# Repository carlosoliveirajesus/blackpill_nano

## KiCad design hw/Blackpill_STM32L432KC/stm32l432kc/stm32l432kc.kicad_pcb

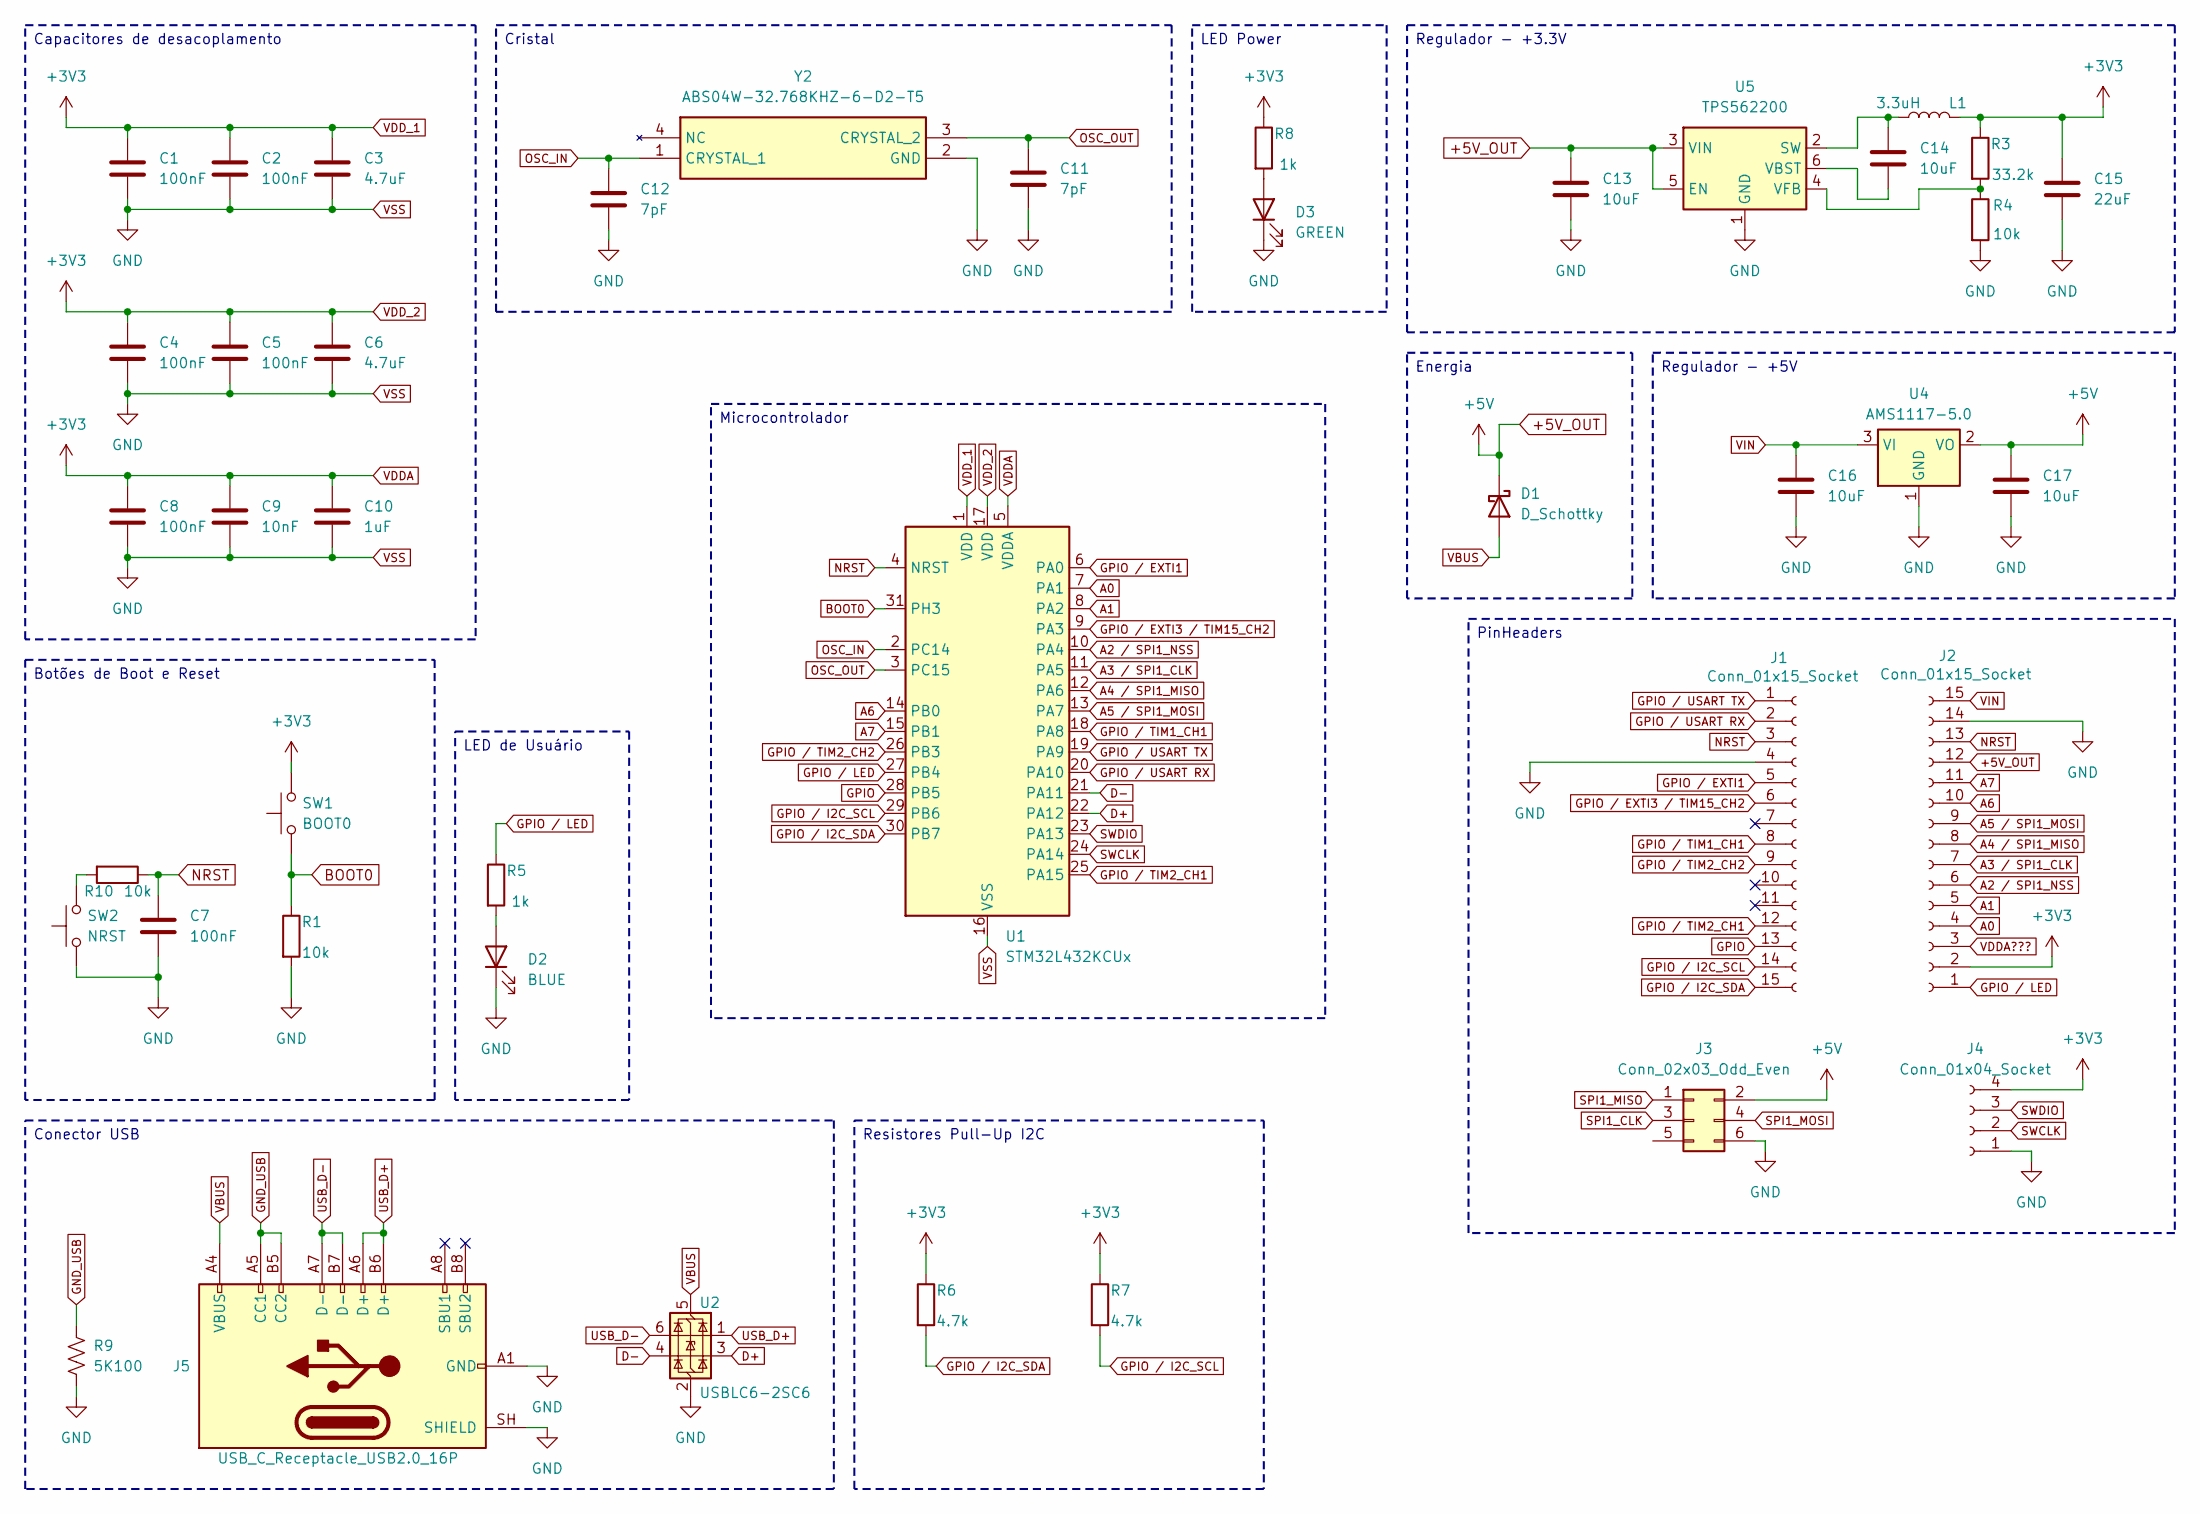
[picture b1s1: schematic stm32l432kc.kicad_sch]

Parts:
C1, C2, C4, C5, C7, C8: 100nF; C_0402_1005Metric
C3, C6: 4.7uF; C_0402_1005Metric
C9: 10nF; C_0402_1005Metric
C10: 1uF; C_0402_1005Metric
C11, C12: 7pF; C_0201_0603Metric
C13, C14, C16, C17: 10uF; C_0402_1005Metric
C15: 22uF; C_0201_0603Metric
D1: D_Schottky; D_SOD-123
D2: BLUE; LED_0603_1608Metric
D3: GREEN; LED_0603_1608Metric
J1, J2: Conn_01x15_Socket; PinHeader_1x15_P2.54mm_Vertical
J3: Conn_02x03_Odd_Even; PinHeader_2x03_P2.54mm_Vertical
J4: Conn_01x04_Socket; PinHeader_1x04_P2.54mm_Horizontal
J5: USB_C_Receptacle_USB2.0_16P; USB_C_Receptacle_GCT_USB4105-xx-A_16P_TopMnt_Horizontal
L1: 3.3uH; L_0603_1608Metric
R1, R4, R10: 10k; R_0402_1005Metric
R3: 33.2k; R_0402_1005Metric
R5, R8: 1k; R_0402_1005Metric
R6, R7: 4.7k; R_01005_0402Metric
R9: 5K100; R_0603_1608Metric_Pad0.98x0.95mm_HandSolder
SW1: BOOT0; SW_SPST_B3U-1000P
SW2: NRST; SW_SPST_B3U-1000P
U1: STM32L432KCUx; QFN-32-1EP_5x5mm_P0.5mm_EP3.45x3.45mm
U2: USBLC6-2SC6; SOT-23-6
U4: AMS1117-5.0; SOT-223-3_TabPin2
U5: TPS562200; SOT-23-6
Y2: ABS04W-32.768KHZ-6-D2-T5; ABS04W32768KHZ6D2T5; Mouser Part Number 815-04W-32.768-6-D2T

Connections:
+5V_OUT: C13.1, C17.1, D1.1 (K), J2.12, J3.2, U4.2 (VO), U5.3 (VIN), U5.5 (EN)
A0: J2.4, U1.7 (PA1)
A1: J2.5, U1.8 (PA2)
A2 / SPI1_NSS: J2.6, U1.10 (PA4)
A3 / SPI1_CLK: J2.7, U1.11 (PA5)
A4 / SPI1_MISO: J2.8, U1.12 (PA6)
A5 / SPI1_MOSI: J2.9, U1.13 (PA7)
A6: J2.10, U1.14 (PB0)
A7: J2.11, U1.15 (PB1)
BOOT0: R1.1, SW1.1, U1.31 (PH3)
D+: U1.22 (PA12), U2.3 (I/O2)
D-: U1.21 (PA11), U2.4 (I/O2)
GND_USB: J5.A5 (CC1), J5.B5 (CC2), R9.1
GPIO: J1.13, U1.28 (PB5)
GPIO / EXTI1: J1.5, U1.6 (PA0)
GPIO / EXTI3 / TIM15_CH2: J1.6, U1.9 (PA3)
GPIO / I2C_SCL: J1.14, R7.2, U1.29 (PB6)
GPIO / I2C_SDA: J1.15, R6.2, U1.30 (PB7)
GPIO / LED: J2.1, R5.1, U1.27 (PB4)
GPIO / TIM1_CH1: J1.8, U1.18 (PA8)
GPIO / TIM2_CH1: J1.12, U1.25 (PA15)
GPIO / TIM2_CH2: J1.9, U1.26 (PB3)
GPIO / USART RX: J1.2, U1.20 (PA10)
GPIO / USART TX: J1.1, U1.19 (PA9)
NRST: C7.1, J1.3, J2.13, R10.1, U1.4 (NRST); also elsewhere on the board
unnamed: D2.2 (A), R5.2
unnamed: D3.2 (A), R8.2
unnamed: R10.2, SW2.2
unnamed: C14.1, L1.2, U5.2 (SW)
unnamed: C14.2, U5.6 (VBST)
unnamed: R3.2, R4.1, U5.4 (VFB)
OSC_IN: C12.1, U1.2 (PC14), Y2.1 (CRYSTAL_1)
OSC_OUT: C11.1, U1.3 (PC15), Y2.3 (CRYSTAL_2)
SPI1_CLK: J3.3
SPI1_MISO: J3.1
SPI1_MOSI: J3.4
SWCLK: J4.2, U1.24 (PA14)
SWDIO: J4.3, U1.23 (PA13)
USB_D+: J5.A6 (D+), J5.B6 (D+), U2.1 (I/O1)
USB_D-: J5.A7 (D-), J5.B7 (D-), U2.6 (I/O1)
VBUS: D1.2 (A), J5.A4 (VBUS), J5.A9 (VBUS), J5.B4 (VBUS), J5.B9 (VBUS), U2.5 (VBUS)
VDDA: C1.1, C2.1, C3.1, C4.1, C5.1, C6.1, C8.1, C9.1, C10.1, C15.1, J2.2, J4.4, L1.1, R3.1, R6.1, R7.1, R8.1, SW1.2, U1.1 (VDD), U1.5 (VDDA), U1.17 (VDD); also elsewhere on the board
VDDA???: J2.3
VIN: C16.1, J2.15, U4.3 (VI)
VSS: C1.2, C2.2, C3.2, C4.2, C5.2, C6.2, C7.2, C8.2, C9.2, C10.2, C11.2, C12.2, C13.2, C15.2, C16.2, C17.2, D2.1 (K), D3.1 (K), J1.4, J2.14, J3.6, J4.1, J5.A1 (GND), J5.A12 (GND), J5.B1 (GND), J5.B12 (GND), J5.SH (SHIELD), R1.2, R4.2, R9.2, SW2.1, U1.16 (VSS), U1.32 (VSS), U1.33 (VSS), U2.2 (GND), U4.1 (GND), U5.1 (GND), Y2.2 (GND)

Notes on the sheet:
LED de Usuário
Energia
Capacitores de desacoplamento
Regulador - +5V
PinHeaders
Conector USB
Resistores Pull-Up I2C
LED Power
Regulador - +3.3V
Botões de Boot e Reset
Microcontrolador
Cristal

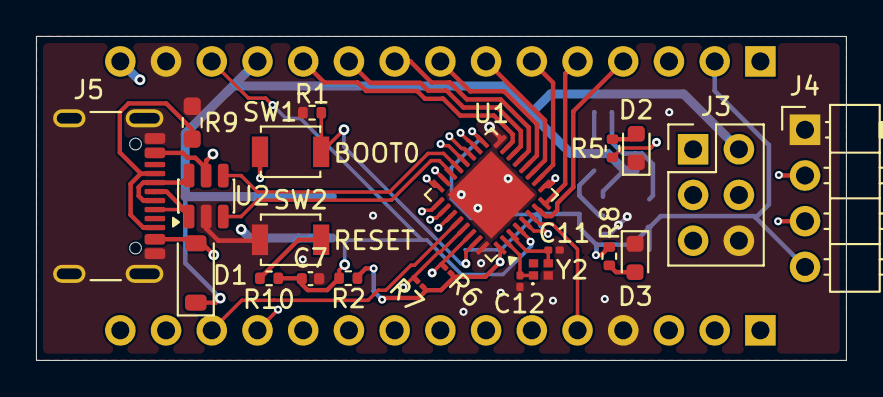
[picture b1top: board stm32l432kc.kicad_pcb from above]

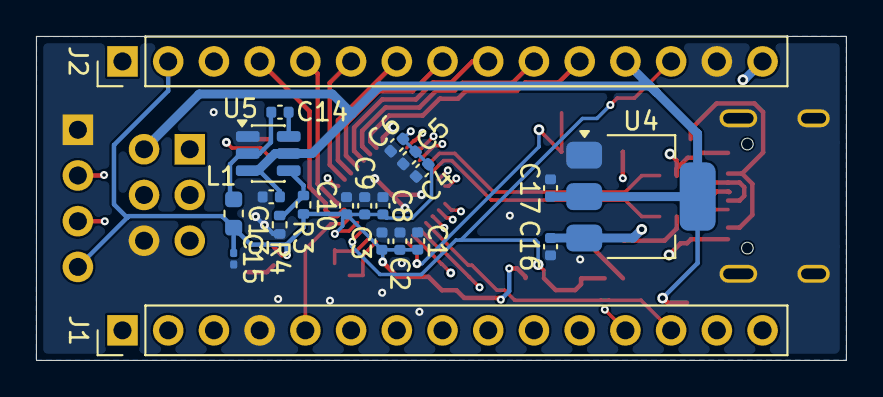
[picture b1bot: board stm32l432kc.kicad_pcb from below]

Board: 4 copper layers, 45.0 x 18.0 mm, 43 parts (21 on the bottom side), 41 nets.

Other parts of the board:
R2: 10k; R_0402_1005Metric

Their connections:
NRST: R2.2; also elsewhere on the board
VDDA: R2.1; also elsewhere on the board

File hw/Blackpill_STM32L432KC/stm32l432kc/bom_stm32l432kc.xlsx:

Reference | Qty | Value | DNP | Exclude from BOM | Exclude from Board | Footprint | Mouser | Datasheet
U4 | 1 | AMS1117-5.0 |  |  |  | Package_TO_SOT_SMD:SOT-223-3_TabPin2 | https://www.digikey.com/en/products/detail/evvo/AMS1117-5-0/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 | http://www.advanced-monolithic.com/pdf/ds1117.pdf
U5 | 1 | TPS562200 |  |  |  | Package_TO_SOT_SMD:SOT-23-6 | https://www.ti.com/product/TPS562200#order-quality | http://www.ti.com/lit/ds/symlink/tps563200.pdf
Y2 | 1 | ABS04W-32.768KHZ-6-D2-T5 |  |  |  | Library:ABS04W32768KHZ6D2T5 | https://br.mouser.com/ProductDetail/ABRACON/ABS04W-32.768KHZ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 | https://abracon.com/datasheets/ABS04W.pdf
D1 | 1 | D_Schottky |  |  |  | Diode_SMD:D_SOD-123 | https://br.mouser.com/ProductDetail/Diodes-Incorporated/B130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 | https://br.mouser.com/datasheet/3/175/1/B120_B-B160_B.pdf
D3 | 1 | GREEN |  |  |  | LED_SMD:LED_0603_1608Metric | https://br.mouser.com/ProductDetail/LITEON/LTST-C190KRKT?qs=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 | https://br.mouser.com/datasheet/3/281/1/LTST_C190KRKT.pdf
D2 | 1 | BLUE |  |  |  | LED_SMD:LED_0603_1608Metric | https://br.mouser.com/ProductDetail/LITEON/LTST-C191KGKT?qs=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 | https://br.mouser.com/datasheet/3/281/1/LTST_C191KGKT.pdf
R1,R2,R4,R10 | 4 | 10k |  |  |  | Resistor_SMD:R_0402_1005Metric | https://br.mouser.com/ProductDetail/YAGEO/RT0402WRD0710KL?qs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 | https://br.mouser.com/datasheet/3/72/1/PYU_RT_1_TO_0_01_ROHS_L.pdf
R5,R8 | 2 | 1k |  |  |  | Resistor_SMD:R_0402_1005Metric | https://br.mouser.com/ProductDetail/YAGEO/RT0402FRE101KL?qs=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 | https://br.mouser.com/datasheet/3/72/1/PYU_RT_1_TO_0_01_ROHS_L.pdf
L1 | 1 | 3.3uH |  |  |  | Inductor_SMD:L_0603_1608Metric | https://br.mouser.com/ProductDetail/Murata-Electronics/LQG18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 | https://br.mouser.com/datasheet/3/76/2/JELF243B_0002.pdf
C15 | 1 | 22uF |  |  |  | Capacitor_SMD:C_0201_0603Metric | https://br.mouser.com/ProductDetail/Murata-Electronics/ZRB18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 | https://br.mouser.com/datasheet/3/76/4/ZRB18AR61C226ME01_01A.pdf
J4 | 1 | Conn_01x04_Socket |  |  |  | Connector_PinHeader_2.54mm:PinHeader_1x04_P2.54mm_Horizontal | https://br.mouser.com/ProductDetail/Amphenol-FCI/68016-104HL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 | https://cdn.amphenol-cs.com/media/wysiwyg/files/drawing/68015.pdf
J3 | 1 | Conn_02x03_Odd_Even |  |  |  | Connector_PinHeader_2.54mm:PinHeader_2x03_P2.54mm_Vertical | https://br.mouser.com/ProductDetail/Amphenol-FCI/10129381-90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 | https://cdn.amphenol-cs.com/media/wysiwyg/files/drawing/1012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
R3 | 1 | 33.2k |  |  |  | Resistor_SMD:R_0402_1005Metric | https://br.mouser.com/ProductDetail/Panasonic/ERA-2APB3322X?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 | https://industrial.panasonic.com/cdbs/www-data/pdf/RDM0000/A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
R6,R7 | 2 | 4.7k |  |  |  | Resistor_SMD:R_0402_1005Metric | https://br.mouser.com/ProductDetail/Panasonic/ERA-2ARC472X?q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 | https://industrial.panasonic.com/cdbs/www-data/pdf/RDM0000/A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
SW1 | 1 | BOOT0 |  |  |  | Button_Switch_SMD:SW_SPST_B3U-1000P | https://br.mouser.com/ProductDetail/Omron-Electronics/B3U-10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 | https://omronfs.omron.com/en_US/ecb/products/pdf/en-b3u.pdf
SW2 | 1 | NRST |  |  |  | Button_Switch_SMD:SW_SPST_B3U-1000P | https://br.mouser.com/ProductDetail/Omron-Electronics/B3U-10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 | https://omronfs.omron.com/en_US/ecb/products/pdf/en-b3u.pdf
C3,C6 | 2 | 4.7uF |  |  |  | Capacitor_SMD:C_0402_1005Metric | https://br.mouser.com/ProductDetail/Murata-Electronics/GRM15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 | https://pim.murata.com/asset/pim4/ceramicCapacitorSMD/GRM155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
J1,J2 | 2 | Conn_01x15_Socket |  |  |  | Connector_PinHeader_2.54mm:PinHeader_1x15_P2.54mm_Vertical | https://br.mouser.com/ProductDetail/Molex/22-28-4153?qs=GAPJ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 | https://www.molex.com/en-us/products/part-detail-pdf/2228415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
J5 | 1 | USB_C_Receptacle_USB2.0_16P |  |  |  | Connector_USB:USB_C_Receptacle_GCT_USB4105-xx-A_16P_TopMnt_Horizontal | https://br.mouser.com/ProductDetail/GCT/USB4110-GF-A?qs=KUoI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 | https://www.mouser.com/catalog/specsheets/GCT_USB4110%20Prod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
C13,C14,C16,C17 | 4 | 10uF |  |  |  | Capacitor_SMD:C_0402_1005Metric | https://br.mouser.com/ProductDetail/KYOCERA-AVX/CM05X5R106M1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 | https://www.mouser.com/catalog/specsheets/KYOCERA_CM105.pdf
C11,C12 | 2 | 7pF |  |  |  | Capacitor_SMD:C_0201_0603Metric | https://br.mouser.com/ProductDetail/TAIYO-YUDEN/MCASU105SCH0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 | https://www.mouser.com/catalog/specsheets/TAIYO-YUDEN_04-29-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
C9 | 1 | 10nF |  |  |  | Capacitor_SMD:C_0402_1005Metric | https://br.mouser.com/ProductDetail/TAIYO-YUDEN/MAASE105SB71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 | https://www.mouser.com/catalog/specsheets/Taiyo_Yuden_c_mlcc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
C10 | 1 | 1uF |  |  |  | Capacitor_SMD:C_0402_1005Metric | https://br.mouser.com/ProductDetail/TAIYO-YUDEN/MAASU105SB71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 | https://www.mouser.com/catalog/specsheets/Taiyo_Yuden_c_mlcc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
C1,C2,C4,C5,C7,C8 | 6 | 100nF |  |  |  | Capacitor_SMD:C_0402_1005Metric | https://br.mouser.com/ProductDetail/TAIYO-YUDEN/MSASL1LHXB51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 | https://www.mouser.com/catalog/specsheets/Tayio_Yuden_110202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
R9 | 1 | 5K100 |  |  |  | Resistor_SMD:R_0603_1608Metric_Pad0.98x0.95mm_HandSolder | https://br.mouser.com/ProductDetail/YAGEO/RC0603FR-075K1L?qs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 | https://www.mouser.com/catalog/specsheets/YAGEO_PYu_RC_Group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
U1 | 1 | STM32L432KCUx |  |  |  | Package_DFN_QFN:QFN-32-1EP_5x5mm_P0.5mm_EP3.45x3.45mm | https://br.mouser.com/ProductDetail/STMicroelectronics/STM32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 | https://www.st.com/resource/en/datasheet/stm32l432kc.pdf
U2 | 1 | USBLC6-2SC6 |  |  |  | Package_TO_SOT_SMD:SOT-23-6 | https://br.mouser.com/ProductDetail/STMicroelectronics/USBLC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 | https://www.st.com/resource/en/datasheet/usblc6-2.pdf

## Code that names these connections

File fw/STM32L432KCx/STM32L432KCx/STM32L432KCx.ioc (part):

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Mcu.Name=STM32L432K(B-C)Ux
Mcu.Package=UFQFPN32
Mcu.UserName=STM32L432KCUx
PA0.Signal=GPIO_Output
PA1.Signal=ADCx_IN6
PA10.Mode=Asynchronous
PA10.Signal=USART1_RX
PA11.Mode=Device
PA11.Signal=USB_DM
PA12.Mode=Device
PA12.Signal=USB_DP
PA13\ (JTMS-SWDIO).Mode=Serial_Wire
PA13\ (JTMS-SWDIO).Signal=SYS_JTMS-SWDIO
PA14\ (JTCK-SWCLK).Mode=Serial_Wire
PA14\ (JTCK-SWCLK).Signal=SYS_JTCK-SWCLK
PA15\ (JTDI).Signal=S_TIM2_CH1
PA2.Signal=ADCx_IN7
PA3.Signal=S_TIM15_CH2
PA4.Mode=NSS_Signal_Hard_Output
PA4.Signal=SPI1_NSS
PA5.Mode=Full_Duplex_Master
PA5.Signal=SPI1_SCK
PA6.Mode=Full_Duplex_Master
PA6.Signal=SPI1_MISO
PA7.Mode=Full_Duplex_Master
PA7.Signal=SPI1_MOSI
PA8.Signal=S_TIM1_CH1
PA9.Mode=Asynchronous
PA9.Signal=USART1_TX
PB0.Signal=ADCx_IN15
PB1.Signal=ADCx_IN16
PB3\ (JTDO-TRACESWO).Signal=S_TIM2_CH2
PB4\ (NJTRST).Signal=GPIO_Output
PB5.Signal=GPIO_Output
PB6.Mode=I2C
PB6.Signal=I2C1_SCL
PB7.Mode=I2C
PB7.Signal=I2C1_SDA
PC14-OSC32_IN\ (PC14).Mode=LSE-External-Oscillator
PC14-OSC32_IN\ (PC14).Signal=RCC_OSC32_IN
PC15-OSC32_OUT\ (PC15).Mode=LSE-External-Oscillator
PC15-OSC32_OUT\ (PC15).Signal=RCC_OSC32_OUT
PH3-BOOT0.GPIOParameters=GPIO_Label
PH3-BOOT0.GPIO_Label=BOOT0
PH3-BOOT0.Signal=GPIO_Input
RCC.HSE_VALUE=8000000
board=custom
